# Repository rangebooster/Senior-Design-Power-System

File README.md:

# Senior-Design-Power-System
This is the repository for the '25 UTV Autonomous Ag. Drone charging station.

Here's the link to the battery charging component: https://www.ti.com/product/BQ24610#product-details

Here's the link to the EVM board for said charging component: https://www.ti.com/tool/BQ24610EVM#description

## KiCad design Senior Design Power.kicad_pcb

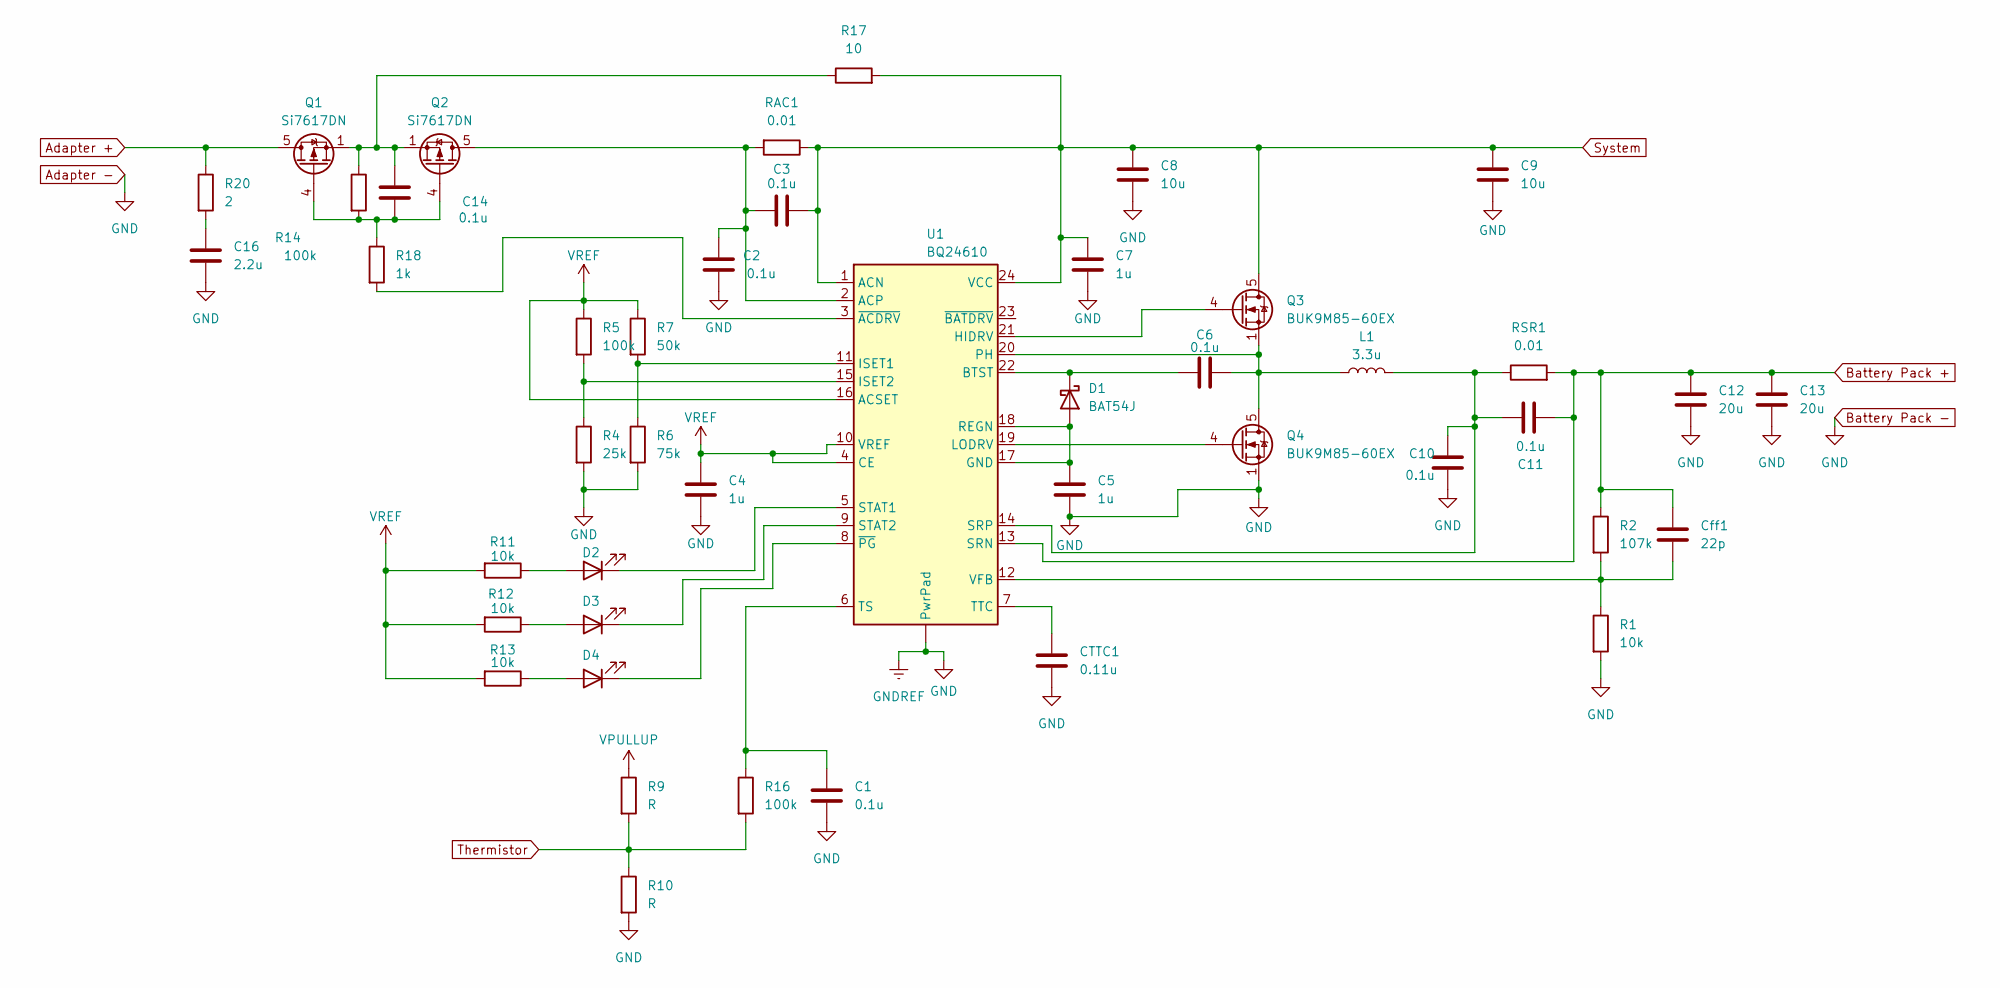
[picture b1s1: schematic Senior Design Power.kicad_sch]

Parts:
C1, C2, C3, C6, C11, C14: 0.1u; C_0201_0603Metric
C4, C5, C7: 1u; C_0201_0603Metric
C8, C9: 10u; C_0201_0603Metric
C10: 0.1u; R_0201_0603Metric
C12, C13: 20u; C_0201_0603Metric
C16: 2.2u; LED_0201_0603Metric
CTTC1: 0.11u; C_0201_0603Metric
Cff1: 22p; C_0201_0603Metric
D1: BAT54J; D_SOD-323F
D2, D3, D4: LED; LED_0201_0603Metric
L1: 3.3u; L_Neosid_SM-PIC0512H
Q1, Q2: Si7617DN; Vishay_PowerPAK_1212-8_Single
Q3, Q4: BUK9M85-60EX; LFPAK33
R1, R11, R12, R13: 10k; R_0201_0603Metric
R2: 107k; R_0201_0603Metric
R4: 25k; R_0201_0603Metric
R5, R14, R16: 100k; R_0201_0603Metric
R6: 75k; R_0201_0603Metric
R7: 50k; R_0201_0603Metric
R9, R10: R; R_0201_0603Metric
R17: 10; R_0201_0603Metric
R18: 1k; R_0201_0603Metric
R20: 2; R_0201_0603Metric
RAC1: 0.01; R_0201_0603Metric
RSR1: 0.01; R_0201_0603Metric
U1: BQ24610; VQFN-24-1EP_4x4mm_P0.5mm_EP2.45x2.45mm

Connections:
Adapter +: Q1.5 (D), R20.1
Adapter -: C1.2, C2.2, C4.2, C5.2, C7.2, C8.2, C9.2, C10.1, C12.2, C13.2, C16.2, CTTC1.2, Q4.1 (S), Q4.2 (S), Q4.3 (S), R1.2, R4.2, R6.2, R10.2, U1. (PwrPad), U1.25 (GND)
Battery Pack +: C11.2, C12.1, C13.1, Cff1.1, R2.1, RSR1.2, U1.13 (SRN)
unnamed: C14.1, Q1.1 (S), Q1.2 (S), Q1.3 (S), Q2.1 (S), Q2.2 (S), Q2.3 (S), R14.1, R17.1
unnamed: C16.1, R20.2
unnamed: C5.1, D1.2 (A), U1.17 (GND), U1.18 (REGN)
unnamed: C6.2, D1.1 (K), U1.22 (BTST)
unnamed: D2.2 (A), R11.1
unnamed: D2.1 (K), U1.5 (STAT1)
unnamed: D3.2 (A), R12.1
unnamed: D3.1 (K), U1.9 (STAT2)
unnamed: D4.2 (A), R13.1
unnamed: D4.1 (K), U1.8 (~PG)
unnamed: C14.2, Q1.4 (G), Q2.4 (G), R14.2, R18.1
unnamed: C2.1, C3.1, Q2.5 (D), RAC1.2, U1.2 (ACP)
unnamed: Q3.4 (G), U1.21 (HIDRV)
unnamed: C6.1, L1.1, Q3.1 (S), Q3.2 (S), Q3.3 (S), Q4.5 (D), U1.20 (PH)
unnamed: Q4.4 (G), U1.19 (LODRV)
unnamed: R6.1, R7.2, U1.11 (ISET1)
unnamed: R4.1, R5.2, U1.15 (ISET2)
unnamed: C10.2, C11.1, L1.2, RSR1.1, U1.14 (SRP)
unnamed: C1.1, R16.1, U1.6 (TS)
unnamed: CTTC1.1, U1.7 (TTC)
unnamed: Cff1.2, R1.1, R2.2, U1.12 (VFB)
unnamed: R18.2, U1.3 (~ACDRV)
System: C3.2, C7.1, C8.1, C9.1, Q3.5 (D), R17.2, RAC1.1, U1.1 (ACN), U1.24 (VCC)
Thermistor: R9.2, R10.1, R16.2
VPULLUP: R9.1
VREF: C4.1, R5.1, R7.1, R11.2, R12.2, R13.2, U1.4 (CE), U1.10 (VREF), U1.16 (ACSET)

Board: 2 copper layers, 45 parts (0 on the bottom side), 28 nets, no tracks yet.

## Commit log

2025-10-21 1st Version
    Added some of the schematic we'll need
2025-10-21 Add files via upload
    Datasheets we're working with
2025-10-23 10/23 Commit - Ty
    10/23 Commit General schematic completed - Ty
2025-11-04 Nov 4th - All but thermistor R values finished
2025-11-05 11/5 - PCB created and schematic footprints added
2025-11-07 Nov 7th - added in grbr data from EVM board
2025-11-07 EVM gbr -> pcb file
2025-11-08 Nov 7th - changed the footprints & corrected unique parts
2025-11-12 Nov 12th
2025-11-12 Nov 12th Newest PCB - Ty
2025-11-13 Nov 13th - Ty
2025-11-14 adding evm board parts to schematic
2025-11-16 updated to include EVM board components
2025-11-17 PCB Review Day, Nov 17th - Ty
2025-11-21 Documents ready for export onto JBL_PCB
2025-11-21 Nov 21st - Final Docs prior to order
